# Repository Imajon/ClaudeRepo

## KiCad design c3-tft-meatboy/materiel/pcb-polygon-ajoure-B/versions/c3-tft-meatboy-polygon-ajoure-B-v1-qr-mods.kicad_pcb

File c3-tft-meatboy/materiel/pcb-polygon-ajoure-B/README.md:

# c3-tft-meatboy — PCB polygon ajouré B (ESP32-C3 SuperMini)

Généré par `../make_kicad_polygon_c3.py B` (routeur `../route_tab.py`). Aperçu : `c3-tft-meatboy-polygon-ajoure-B.svg`.

**= ajouré A + traits déco** : bandes de 2 mm à 45° (pas 4 mm) sur la partie haute (au-dessus de y = 31,5 mm, hors écran),
en **cuivre nu** (F.Cu + ouverture F.Mask, sans net). Coupées autour des pistes, pastilles, vias, trous et sérigraphie.

**+ languette d'accroche** détachable (façon Pocket Operator, comme l'ajouré C) : oblong 66 × 10,75 mm, trou 26 × 4 mm + demi-cercle R3,5
(crochet de rayon), 3 attaches de 2 mm sur les pointes du haut (pointes tronquées de 0,55 mm), bord cuivre nu + stries.

- **C3 SuperMini** au dos, en bas au centre ; pointe du bas coupée à plat (y = 73 mm) : l'USB-C arrive au bord de la carte.
- **QR code** cuivre au dos, **35,4 mm** (plaque 38 mm, de y = 10 à 48, au maximum entre le bord haut et le module) → https://studioeya.com (miroir, se lit de derrière). Pas d'étiquette (plus de place).
- **4 pastilles de fil** IO21/IO20 (gauche), IO0/IO8 (droite).
- **LED optionnelles** en haut (une par pointe : GAUCHE, DROITE, SAUT), CMS 1206 : +3V3 → R → LED → fil du bouton.
  Bouton appuyé = LED allumée, sans changer le code. Sans LED ni R, rien ne change.
  R ≈ 1 kΩ (LED rouge ~1,5 mA) ; descendre à 330 Ω pour plus de lumière. Pastille 1 de la LED (trait sérigraphié) = cathode.
- GND relié par les plans de masse des deux faces (pas de pistes GND).
- DRC : 0 non connecté ; 1 remarque (frein thermique de la broche GND de l'écran au dos, déjà reliée par la face avant). BL de l'écran (J3 broche 8) relié au +3V3.
- Versions précédentes : `versions/` (v1-qr-mods : QR 14 mm vers le GitHub ; v2-qr-studioeya : sans languette).

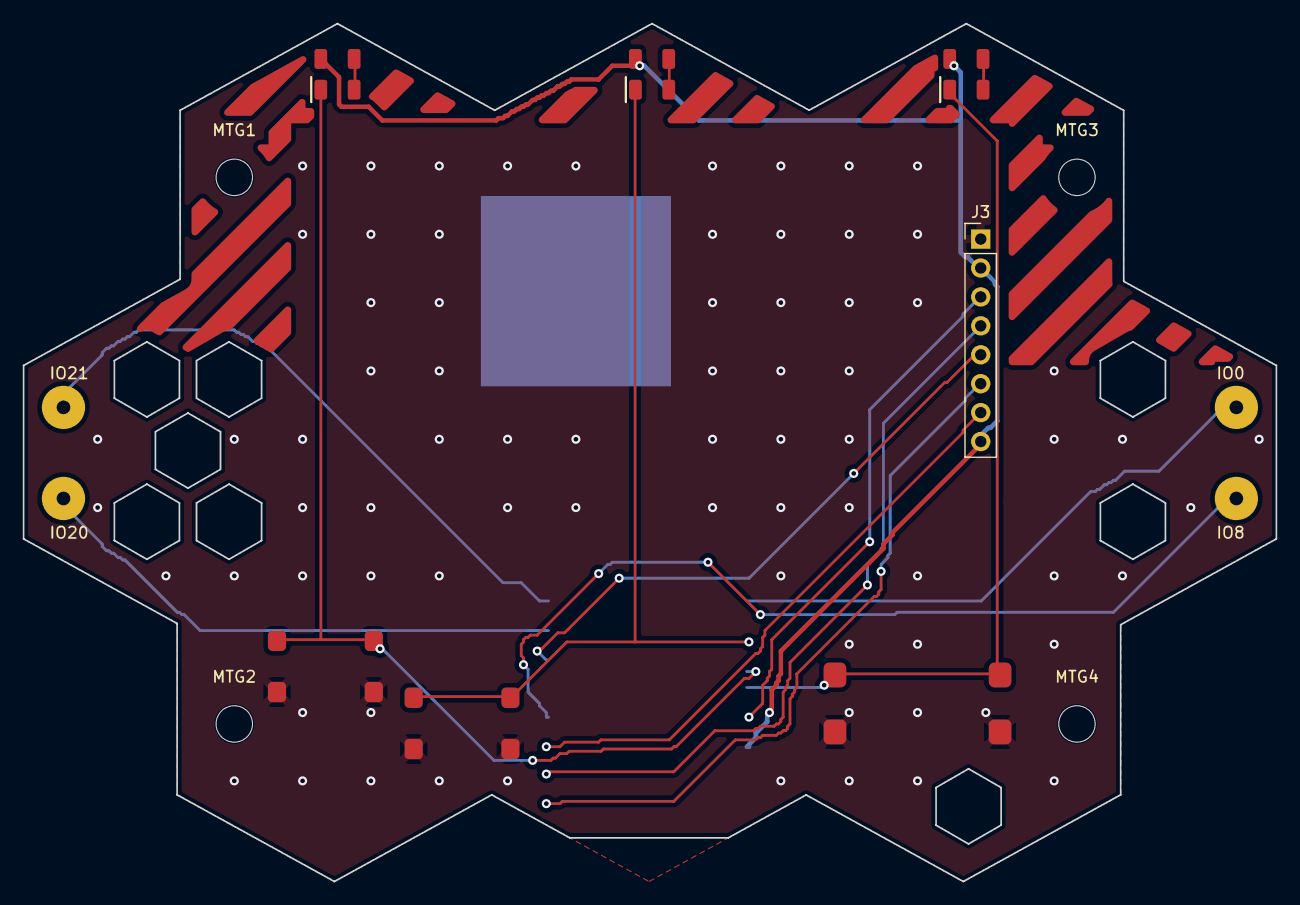
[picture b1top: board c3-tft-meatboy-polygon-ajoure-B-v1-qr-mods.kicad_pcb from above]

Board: 2 copper layers, 110.0 x 75.3 mm, 19 parts (1 on the bottom side), 17 nets.

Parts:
D1, D2, D3: LED_1206_3216Metric
J3: PinHeader_1x08_P2.54mm_Vertical
MTG1, MTG2, MTG3, MTG4: MountingHole_3.2mm_M3
P1, P2, P3, P4: WirePad_3.8mm
R1, R2, R3: R_1206_3216Metric
SW1, SW2, SW3: (no value)
U1: ESP32-C3_SuperMini_SMD

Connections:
+3V3: J3.2, J3.8, R1.1, R2.1, R3.1, U1.6
CS: J3.7, U1.14
DC: J3.6, U1.16
DROITE: D2.1, SW2.1, U1.2
GAUCHE: D1.1, SW1.1, U1.3
GND: J3.1, SW1.2, SW2.2, SW3.2, U1.7
IO0: P3.1, U1.1
IO8: P4.1, U1.13
IO20: P2.1, U1.10
IO21: P1.1, U1.9
LED_DROITE: D2.2, R2.2
LED_GAUCHE: D1.2, R1.2
LED_SAUT: D3.2, R3.2
MOSI: J3.4, U1.15
RST: J3.5, U1.11
SAUT: D3.1, SW3.1, U1.4
SCLK: J3.3, U1.5

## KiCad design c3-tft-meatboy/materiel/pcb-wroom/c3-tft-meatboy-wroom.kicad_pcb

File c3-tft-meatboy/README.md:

# Brique — la console de jeu que les enfants soudent eux-mêmes

**Brique** est une petite console de jeu portable à base d'**ESP32-C3** et d'un **écran TFT 2"**, conçue pour des ateliers avec des enfants (CM1 → 4ᵉ). Chaque enfant monte et soude sa propre console, puis joue à **Pixel Run**, un jeu de plateforme écrit pour la console.

Prochaine étape : laisser les enfants **créer leurs propres niveaux et règles avec une IA**, depuis un navigateur, sans rien installer.

---

## Le concept

Trois composants, trois boutons, un fer à souder. L'objectif : un objet simple à assembler, mais qui donne un vrai jeu fluide une fois allumé.

## Le matériel

| Composant | Rôle |
|---|---|
| ESP32-C3 Super Mini | Microcontrôleur Wi-Fi / ESP-NOW, USB-C |
| Écran TFT 2" ST7789 (SPI, 320×240) | Affichage |
| 3 boutons-poussoirs | Gauche (GPIO2), Droite (GPIO1), Saut (GPIO3) |
| Plaque à pastilles ou PCB hexagonal | Support |

## L'atelier

Les enfants partent des composants en vrac et repartent avec une console qui marche.

## Version 1 — prototype sur plaque à pastilles

Câblage fil à fil au dos, écran et boutons en façade.

## Version 2 — PCB hexagonal

Un PCB dédié en forme de briques hexagonales : moins de fils, montage plus rapide en atelier.

Fichiers KiCad et SVG du boîtier : [`materiel/`](materiel/).

## Le jeu : Pixel Run

- **100 niveaux** variés (ressorts, pics, blocs tombants, ennemis, scies…), étoiles à collecter, drapeau final.
- **Mode 2 joueurs** sans fil (ESP-NOW) : course avec le fantôme de l'adversaire.
- **Mini-jeux** bonus toutes les 10 étapes : Pong, Casse-brique, Invaders.
- **Quiz CM2** (maths, français, anglais) entre les niveaux, avec récompenses visuelles.
- **Classement partagé** entre consoles, boutique de skins, mascotte animée.
- Progression sauvegardée en mémoire flash.

## Compiler et flasher

Sketch Arduino : [`c3-tft-meatboy.ino`](c3-tft-meatboy.ino) (carte ESP32C3 Dev Module).

```bat
compiler-upload-c3-tft-meatboy.bat
```

Détails techniques et historique des versions : [`CONTEXTE.md`](CONTEXTE.md).

## La suite : créer son jeu avec l'IA

Idée : un firmware fixe (moteur, affichage, sons) et une IA qui génère uniquement **les niveaux et les règles** sous forme de données, envoyées à la console en quelques millisecondes depuis une page web. Le but n'est pas d'apprendre la syntaxe, mais de montrer aux enfants qu'ils peuvent **décrire, tester et corriger** un jeu qu'ils ont imaginé.

---

*AntiFaktory — 2026*

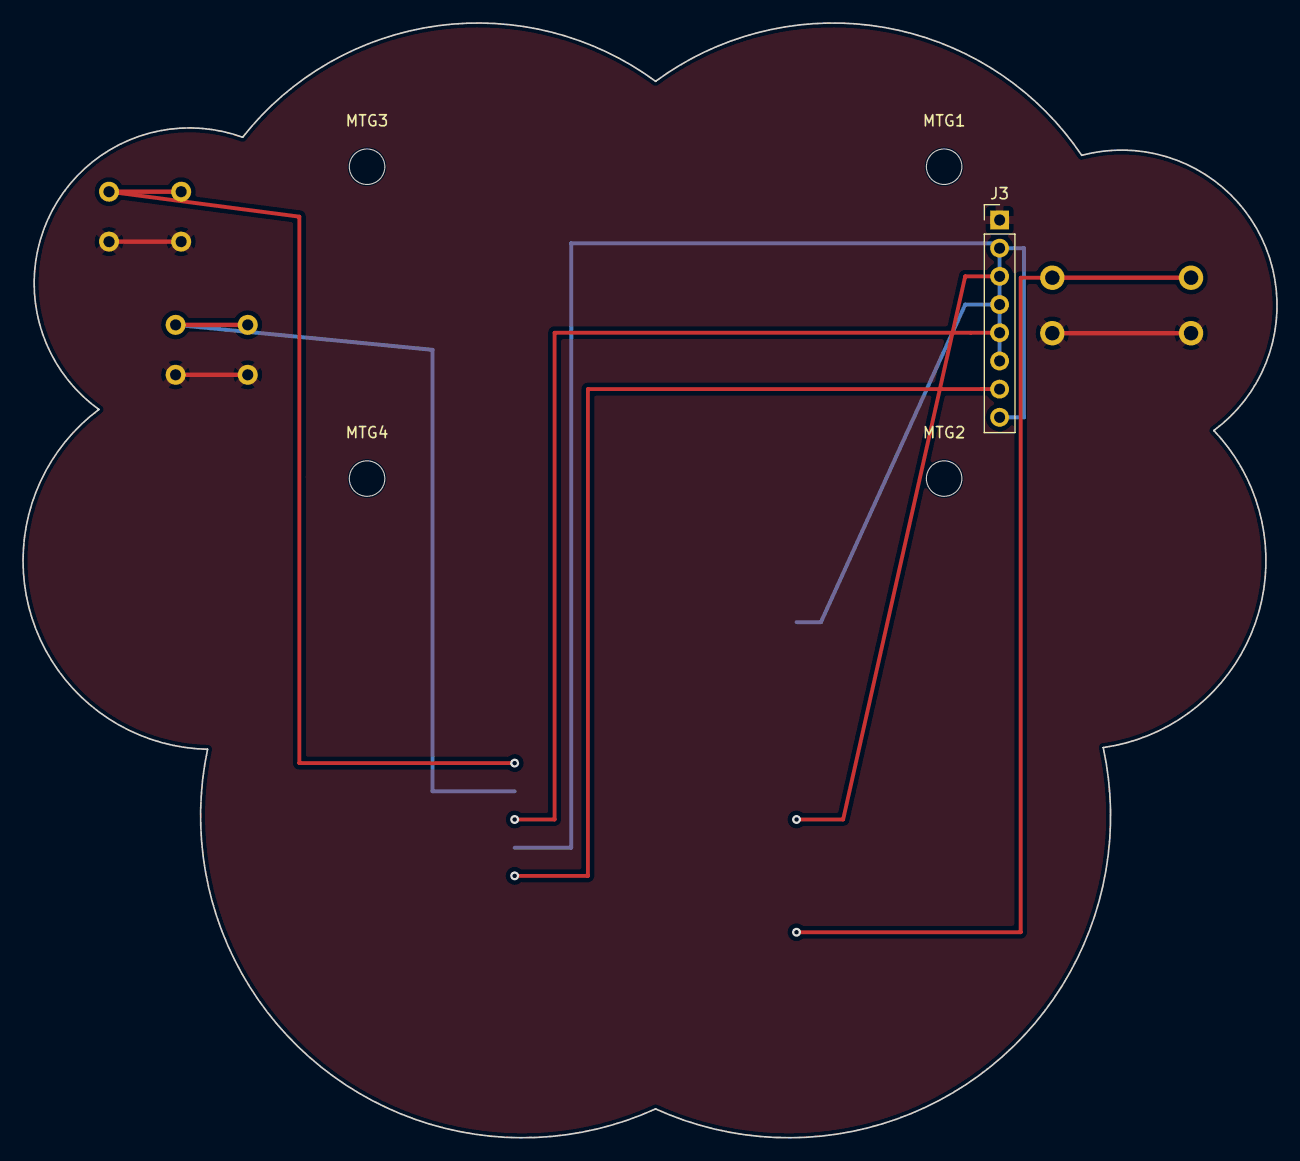
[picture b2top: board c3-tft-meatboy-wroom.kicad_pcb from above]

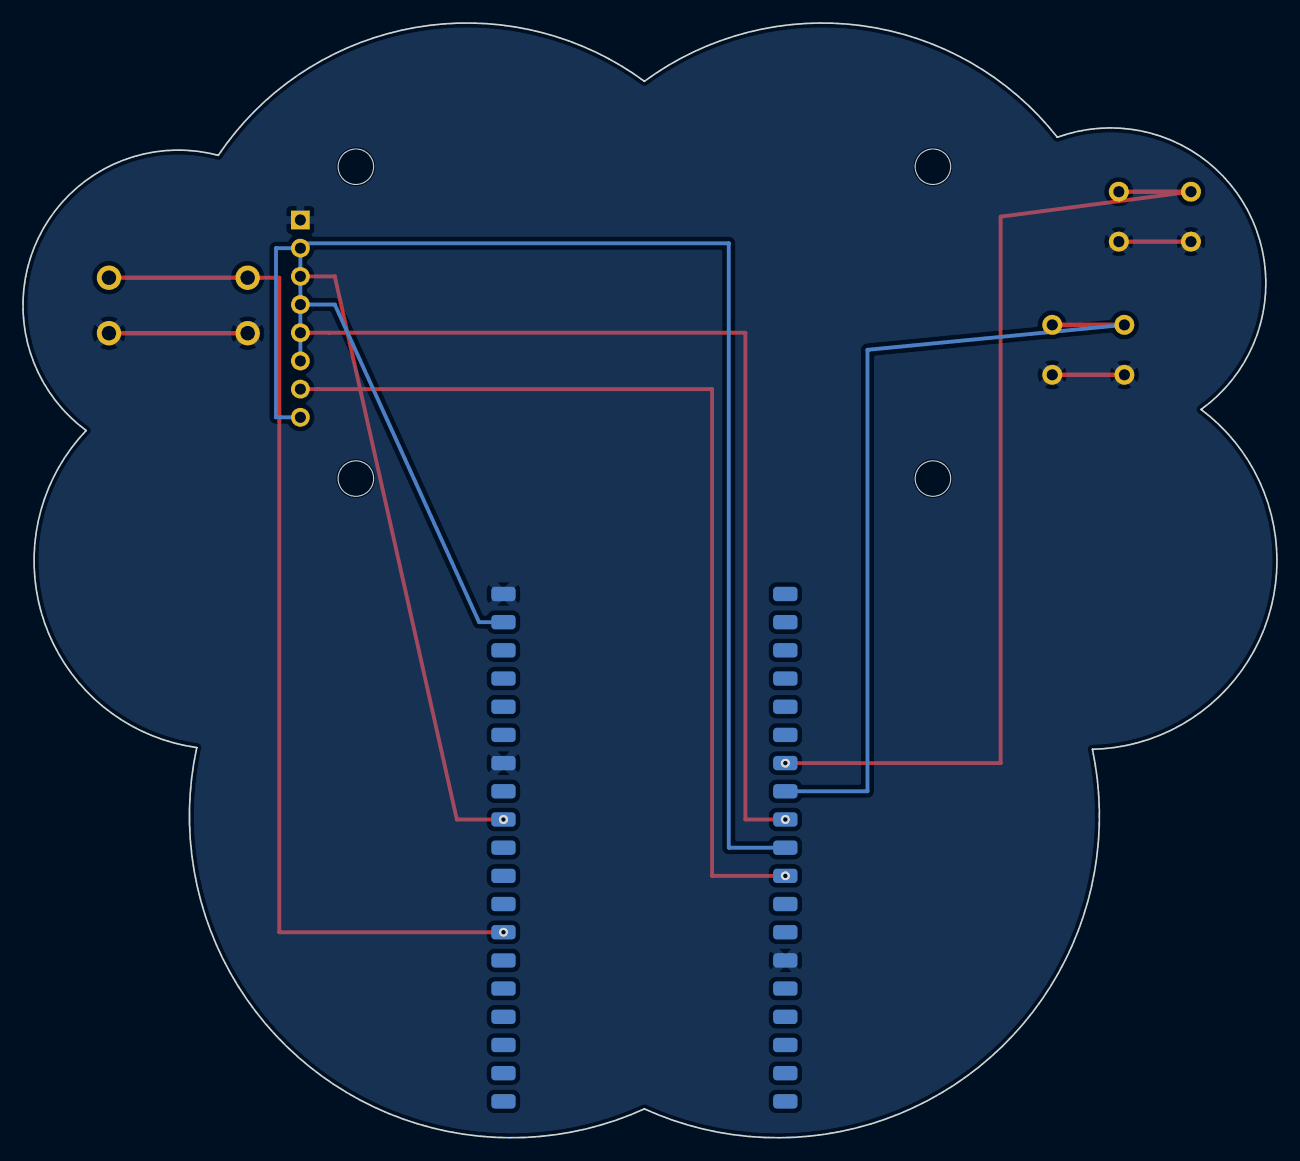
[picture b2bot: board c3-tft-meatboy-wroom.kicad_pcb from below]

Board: 2 copper layers, 113.0 x 100.4 mm, 10 parts (2 on the bottom side), 10 nets.

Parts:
J1, J2: (no value)
J3: PinHeader_1x08_P2.54mm_Vertical
MTG1, MTG2, MTG3, MTG4: MountingHole_3.2mm_M3
SW1, SW2, SW3: (no value)

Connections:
+3V3: J1.1, J3.2, J3.8
GND: J1.14, J2.1, J2.7, J3.1, SW1.2, SW2.2, SW3.2
GPIO4_SAUT: J2.13, SW3.1
GPIO18_SCLK: J2.9, J3.3
GPIO23_MOSI: J2.2, J3.4
GPIO25_RST: J1.9, J3.5
GPIO26_DC: J1.10, J3.6
GPIO27_CS: J1.11, J3.7
GPIO32_DROITE: J1.7, SW2.1
GPIO33_GAUCHE: J1.8, SW1.1

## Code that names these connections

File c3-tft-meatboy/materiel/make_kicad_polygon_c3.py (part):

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PCB = f"{D}/{NAME}.kicad_pcb"
KICAD_CLI = r"C:\Users\info\AppData\Local\Programs\KiCad\10.0\bin\kicad-cli.exe"
uid = lambda: str(uuid.uuid4())
RENAME = {"GPIO32_DROITE": "DROITE", "GPIO33_GAUCHE": "GAUCHE", "GPIO4_SAUT": "SAUT", "GPIO18_SCLK": "SCLK",
          "GPIO23_MOSI": "MOSI", "GPIO25_RST": "RST", "GPIO26_DC": "DC", "GPIO27_CS": "CS"}

s = open(SRC, encoding="utf-8").read()
for a, b in RENAME.items():
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                         shape="circle" if shape == "circle" else "rect", tht=kind == "thru_hole", front='"F.Cu"' in p))

# ---------- ESP32-C3 SuperMini au dos (identique a make_kicad_tab.py) ----------
J1 = [None, "DROITE", "GAUCHE", "SAUT", "SCLK", "+3V3", "GND", None]      # GPIO0,1,2,3,4,3V3,GND,5V
J2 = [None, None, "RST", None, None, "CS", "MOSI", "DC"]                  # GPIO21,20,10,9,8,7,6,5
if V:                                                                     # pastilles de fil du dessin ajoure
    J1[0], J2[0], J2[1], J2[4] = "IO0", "IO21", "IO20", "IO8"
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
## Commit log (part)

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2026-06-11 Lidar V1
2026-06-11 EspNowV1
2026-06-11 SentinelV2
2026-06-11 Remove node_modules from tracking
2026-06-21 Echec enfant
2026-06-21 Echec enfant V2
2026-06-21 Echec enfant V3
